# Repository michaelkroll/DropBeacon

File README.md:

DropBeacon
==========

An iBeacon compatible beacon based on Bluegiga's BLE112 BLE4.0 Module

Details see on Michael Kroll's Blog at http://www.mkroll.mobi/?page_id=1693
 
Photos
===

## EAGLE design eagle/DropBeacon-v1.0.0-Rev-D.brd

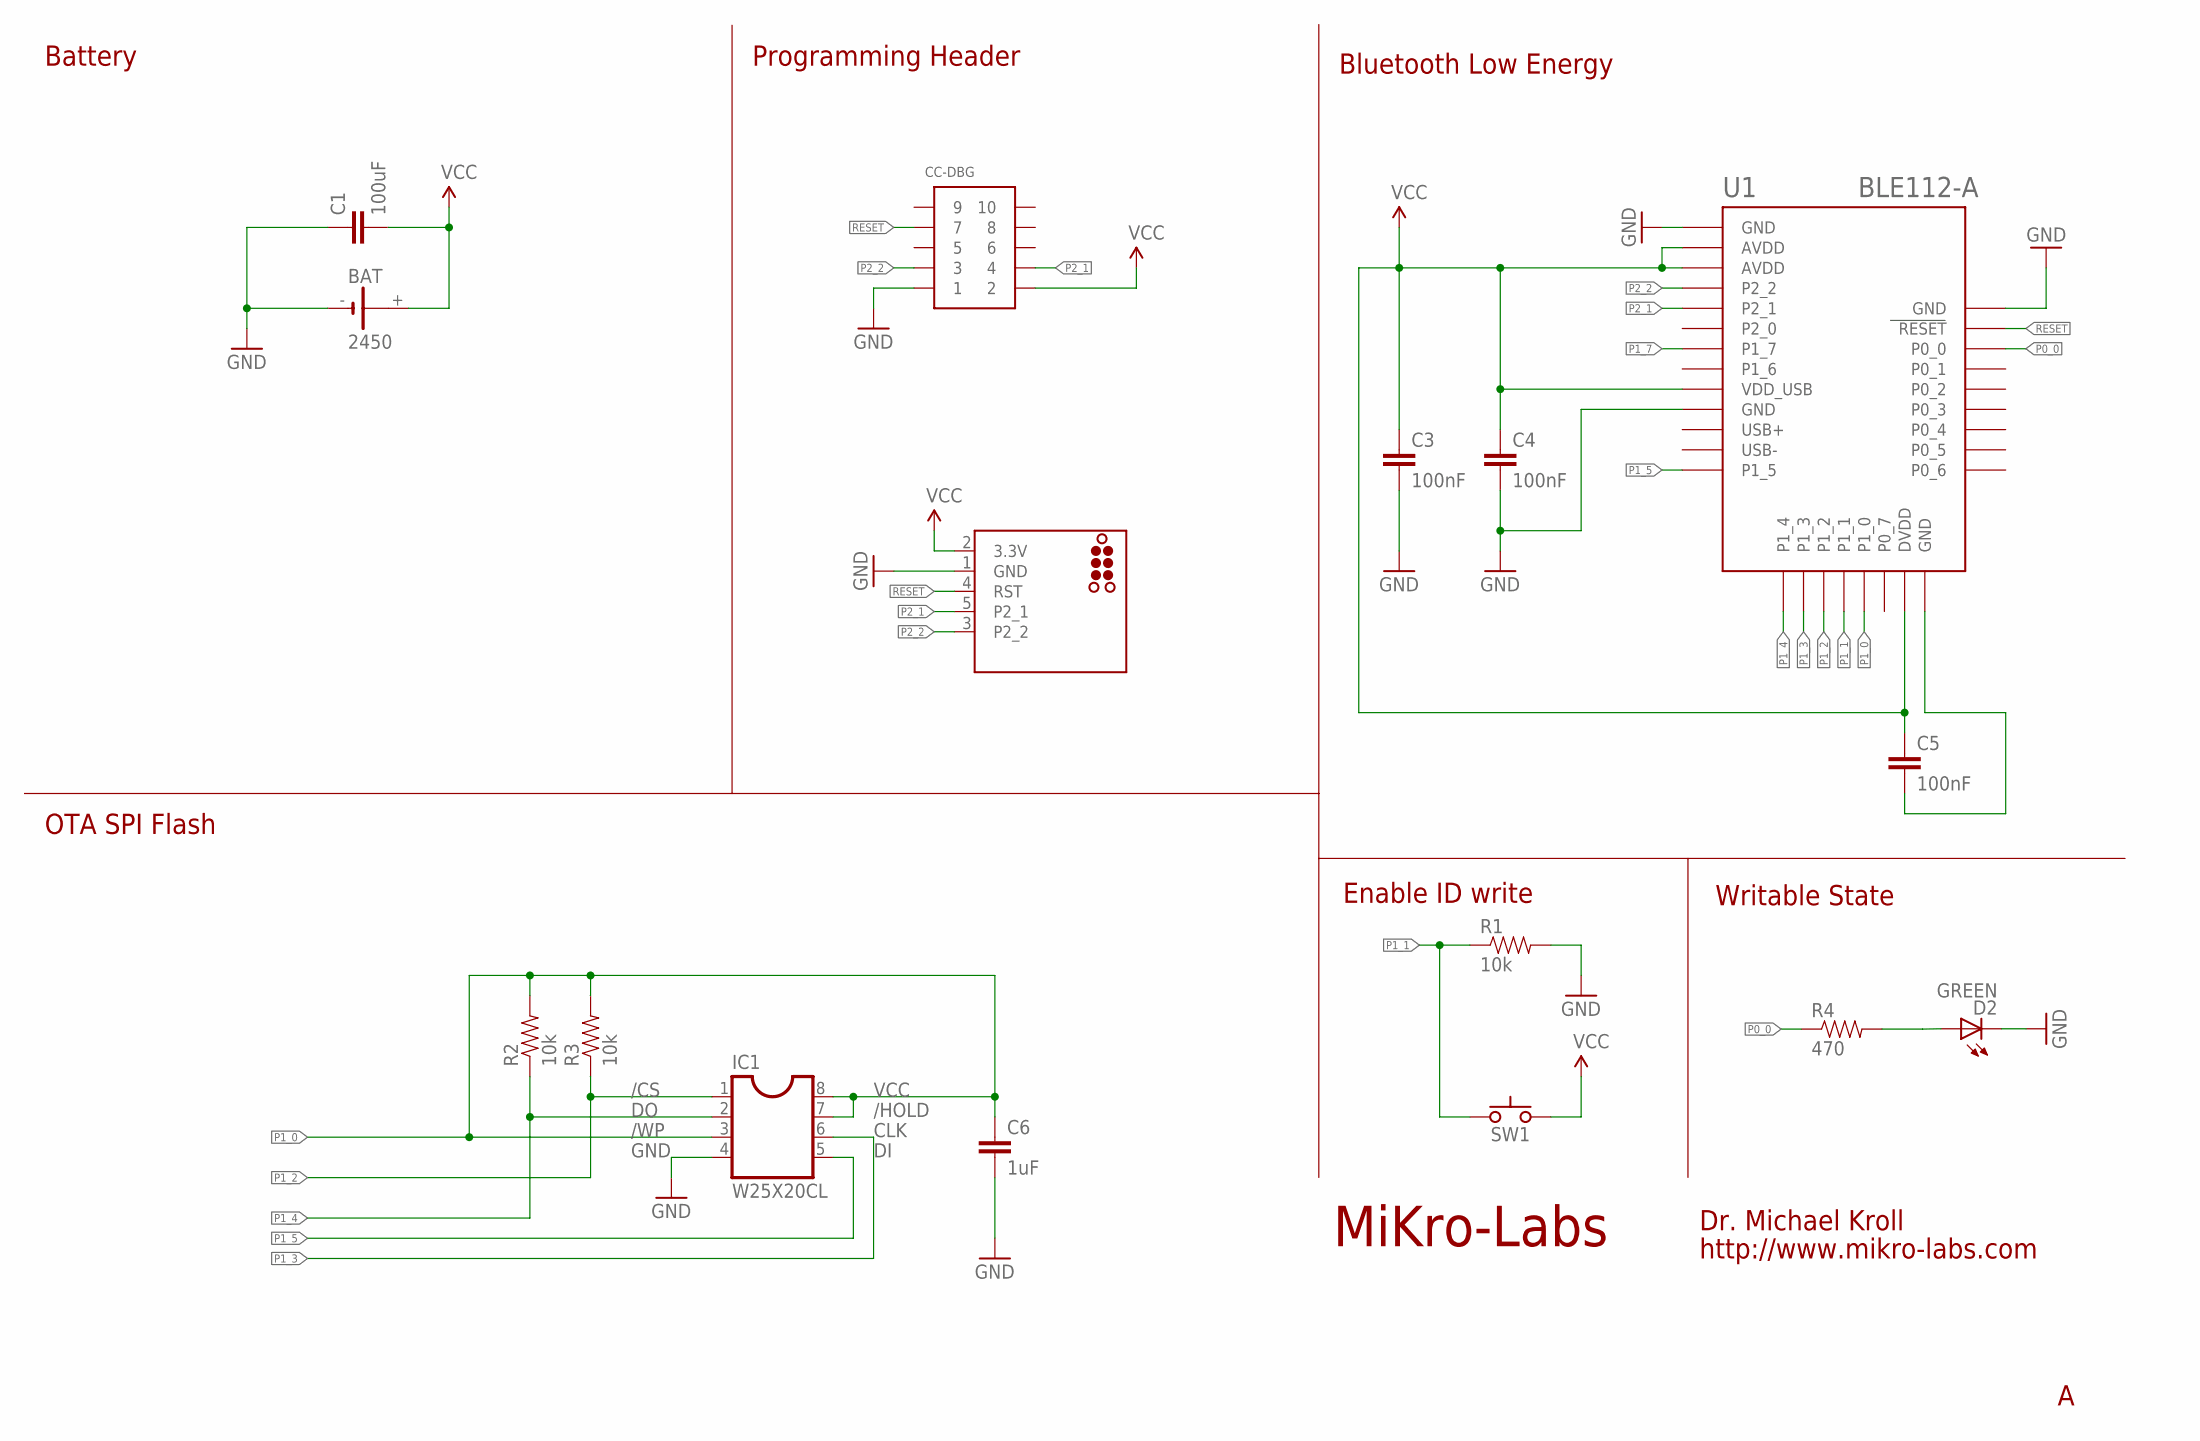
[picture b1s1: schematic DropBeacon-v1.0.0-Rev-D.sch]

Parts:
BAT: 2450; KZH24SMD
C1: 100uF; 1206
C3, C4, C5: 100nF; 0603-CAP
C6: 1uF; 0603-CAP
CC-DBG: CONN_5-2-FTSH-V; FTSH-105-DV
CC-DEBUGGER: TC2030-CC-DEBUGGER; TC2030-MCP-NL
D2: GREEN; LED-0603
IC1: W25X20CL; SO-8
R1, R2, R3: 10k; 0603-RES
R4: 470; 0603-RES
SW1: B3U-1000P
U1: BLE112-A

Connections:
GND: BAT.-, C1.1, C3.2, C4.2, C6.2, CC-DBG.1, CC-DEBUGGER.1 (GND), D2.C, IC1.4, R1.2, U1.GND, U1.GND@2 (GND), U1.GND@4 (GND)
unnamed: D2.A, R4.2
unnamed: C5.2, U1.GND@3 (GND)
P0_0: R4.1, U1.P0_0
P1_0: C6.1, IC1.3, IC1.7, IC1.8, R2.2, R3.2, U1.P1_0
P1_1: R1.1, SW1.1, U1.P1_1
P1_2: IC1.1, R3.1, U1.P1_2
P1_3: IC1.6, U1.P1_3
P1_4: IC1.2, R2.1, U1.P1_4
P1_5: IC1.5, U1.P1_5
P1_7: U1.P1_7
P2_1: CC-DBG.4, CC-DEBUGGER.5 (P2_1), U1.P2_1
P2_2: CC-DBG.3, CC-DEBUGGER.3 (P2_2), U1.P2_2
RESET: CC-DBG.7, CC-DEBUGGER.4 (RST), U1.RESET
VCC: BAT.+, C1.2, C3.1, C4.1, C5.1, CC-DBG.2, CC-DEBUGGER.2 (3.3V), SW1.2, U1.AVDD, U1.AVDD@2 (AVDD), U1.DVDD, U1.VDD_USB

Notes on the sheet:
Dr. Michael Kroll
http://www.mikro-labs.com
OTA SPI Flash
Programming Header
Battery
Bluetooth Low Energy
Enable ID write
Writable State
MiKro-Labs
VCC
/HOLD
CLK
GND
/WP
/CS

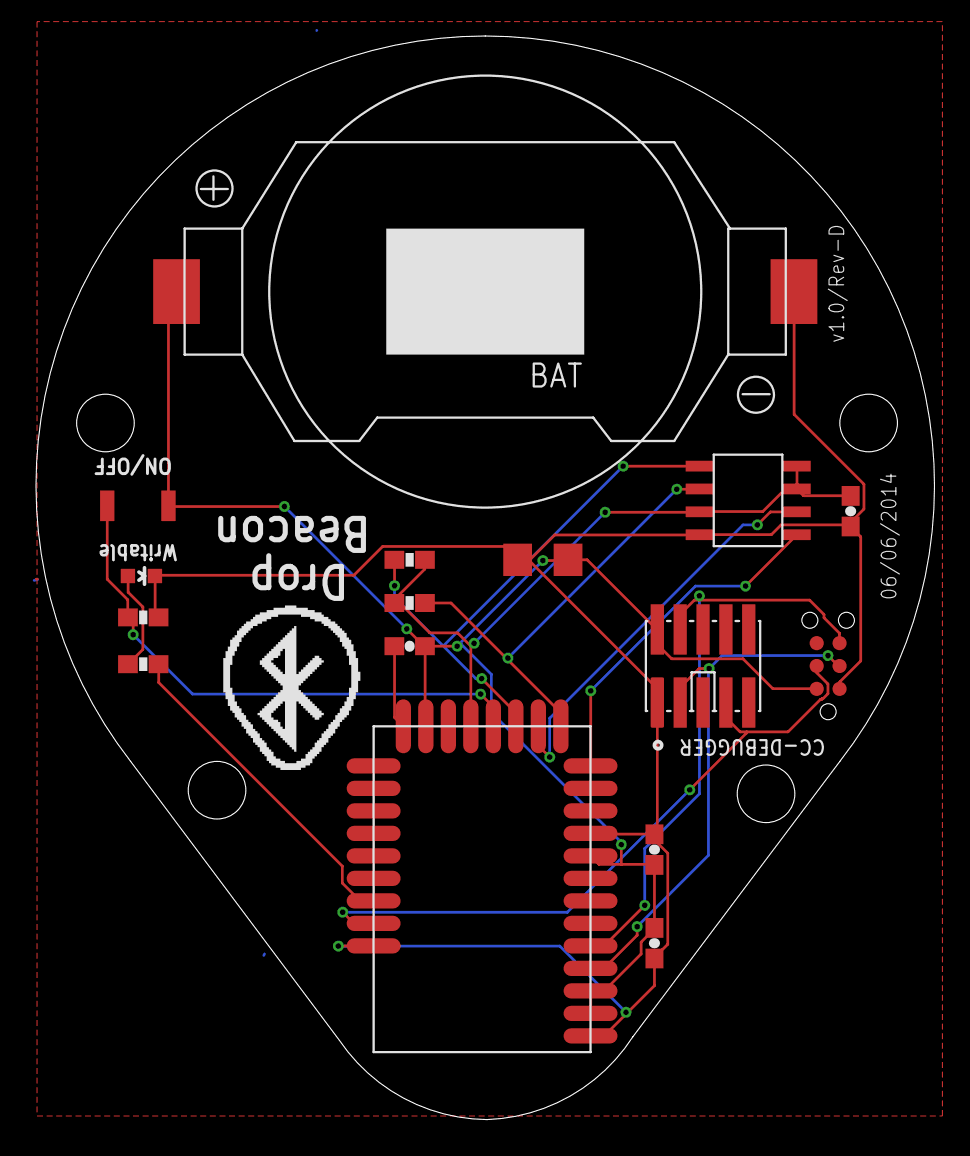
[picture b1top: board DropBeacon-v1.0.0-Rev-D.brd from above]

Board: 4 copper layers, 49.9 x 60.2 mm, 19 parts (2 on the bottom side), 14 nets.

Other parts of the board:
U$1: MIKROLABS-LOGO-LARGE
U$2: MIKROLABS-URL
U$3: DROPBEACON-MINI

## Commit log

2014-06-28 Initial commit. Details are available at: http://www.mkroll.mobi/?page_id=1693
2014-07-21 XML syntax error fixed.
2014-07-26 Advertisement rate changed. New firmware v1.1 with adjusted ADV rate added.
2014-08-13 new firmwares aded.
2014-10-13 Changed the firmware to use SDK1.3.1. Changed the advertisment interval to get more than 3 months of battery life.

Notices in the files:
parts and their libraries:
SparkFun-Capacitors: Licensing: CC v3.0 Share-Alike You are welcome to use this library for commercial purposes.
Tag-Connect: ©2009 ROFA.cz - modified and updated by Robert Darlington ‹rdarlington@gmail.com›
